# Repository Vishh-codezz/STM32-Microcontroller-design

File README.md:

# STM32-Microcontroller-design
This project is about the STM32 microcontroller board design.

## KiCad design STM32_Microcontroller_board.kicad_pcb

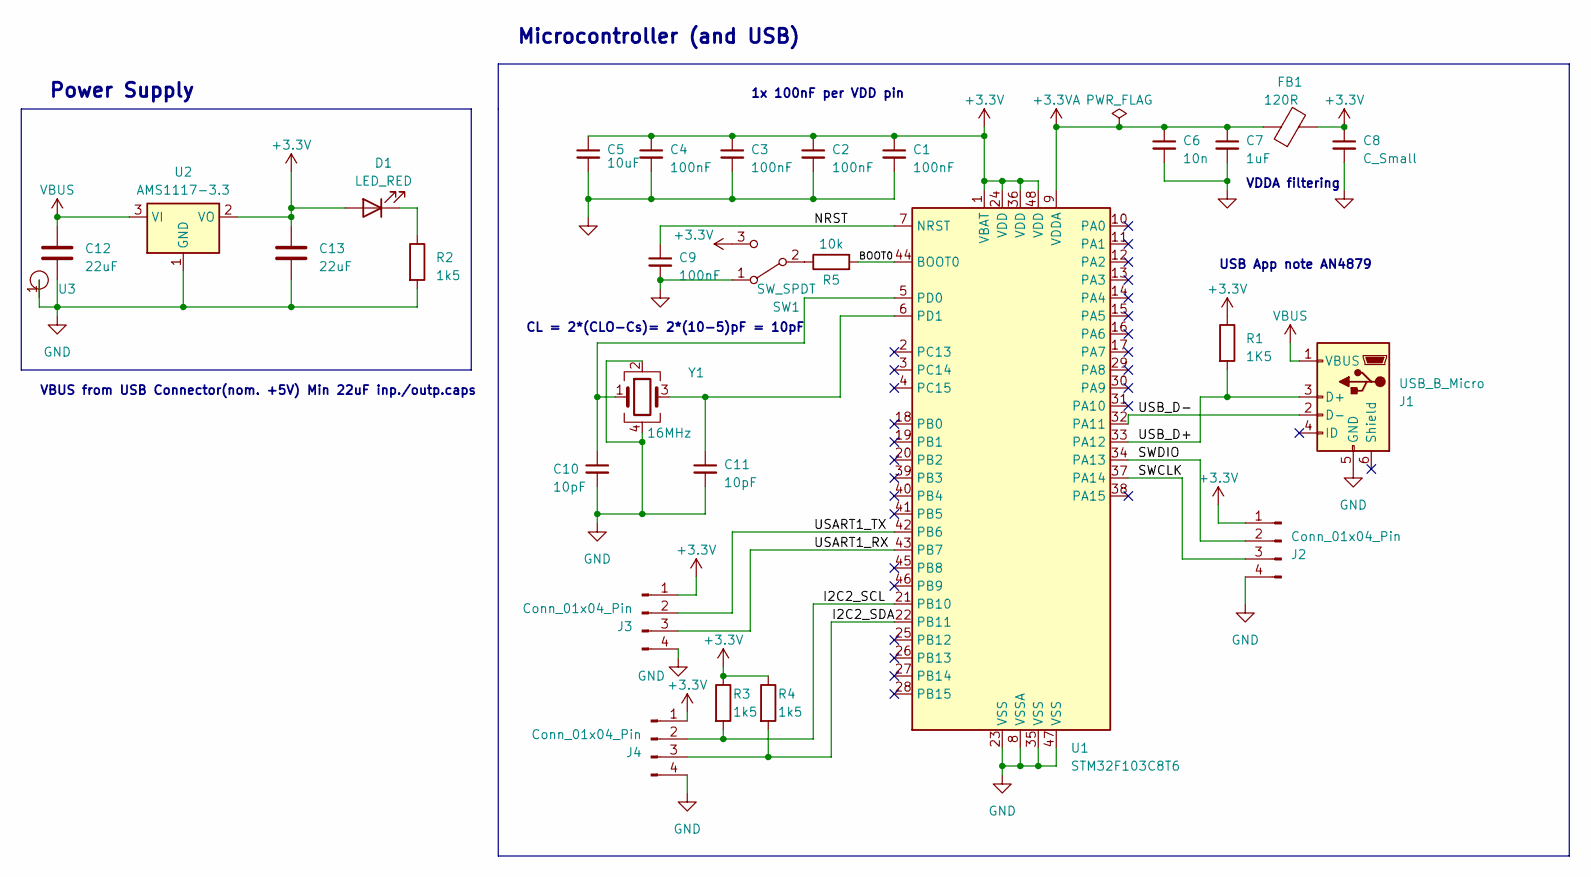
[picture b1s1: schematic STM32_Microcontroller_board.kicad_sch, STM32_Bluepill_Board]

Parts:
C1, C2, C3, C4, C9: 100nF; C_0402_1005Metric
C5: 10uF; C_0603_1608Metric
C6: 10n; C_0402_1005Metric
C7: 1uF; C_0402_1005Metric
C8: C_Small; C_0402_1005Metric
C10, C11: 10pF; C_0402_1005Metric
C12, C13: 22uF; C_0805_2012Metric
D1: LED_RED; LED_0603_1608Metric
FB1: 120R; L_0603_1608Metric
J1: USB_B_Micro; USB_Micro-B_Wuerth_629105150521
J2, J3, J4: Conn_01x04_Pin; PinHeader_1x04_P2.54mm_Vertical
R1: 1K5; R_0402_1005Metric
R2, R3, R4: 1k5; R_0402_1005Metric
R5: 10k; R_0402_1005Metric
SW1: SW_SPDT; SW_SPDT_PCM12
U1: STM32F103C8T6; LQFP-48_7x7mm_P0.5mm
U2: AMS1117-3.3; SOT-223-3_TabPin2
U3: Soldernail
Y1: 16MHz; Crystal_SMD_3225-4Pin_3.2x2.5mm

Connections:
+3.3V: C1.1, C2.1, C3.1, C4.1, C5.1, C8.1, C13.1, D1.2 (A), FB1.2, J2.1, J3.1, J4.1, R1.1, R3.1, R4.1, SW1.3 (C), U1.1 (VBAT), U1.24 (VDD), U1.36 (VDD), U1.48 (VDD), U2.2 (VO)
+3.3VA: C6.1, C7.1, FB1.1, U1.9 (VDDA)
/BOOT0: R5.2, U1.44 (BOOT0)
/I2C2_SCL: J4.2, R3.2, U1.21 (PB10)
/I2C2_SDA: J4.3, R4.2, U1.22 (PB11)
/NRST: C9.1, U1.7 (NRST)
/SWCLK: J2.3, U1.37 (PA14)
/SWDIO: J2.2, U1.34 (PA13)
/USART1_RX: J3.3, U1.43 (PB7)
/USART1_TX: J3.2, U1.42 (PB6)
/USB_D+: J1.3 (D+), R1.2, U1.33 (PA12)
/USB_D-: J1.2 (D-), U1.32 (PA11)
GND: C1.2, C2.2, C3.2, C4.2, C5.2, C6.2, C7.2, C8.2, C9.2, C10.2, C11.2, C12.2, C13.2, J1.5 (GND), J2.4, J3.4, J4.4, R2.2, SW1.1 (A), U1.8 (VSSA), U1.23 (VSS), U1.35 (VSS), U1.47 (VSS), U2.1 (GND), U3.1, Y1.2, Y1.4
unnamed: D1.1 (K), R2.1
unnamed: R5.1, SW1.2 (B)
unnamed: C10.1, U1.5 (PD0), Y1.1
unnamed: C11.1, U1.6 (PD1), Y1.3
VBUS: C12.1, J1.1 (VBUS), U2.3 (VI)

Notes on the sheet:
USB App note AN4879
Microcontroller (and USB)
VDDA filtering
CL = 2*(CLO-Cs)= 2*(10-5)pF = 10pF
VBUS from USB Connector(nom. +5V) Min 22uF inp./outp.caps
Power Supply
1x 100nF per VDD pin

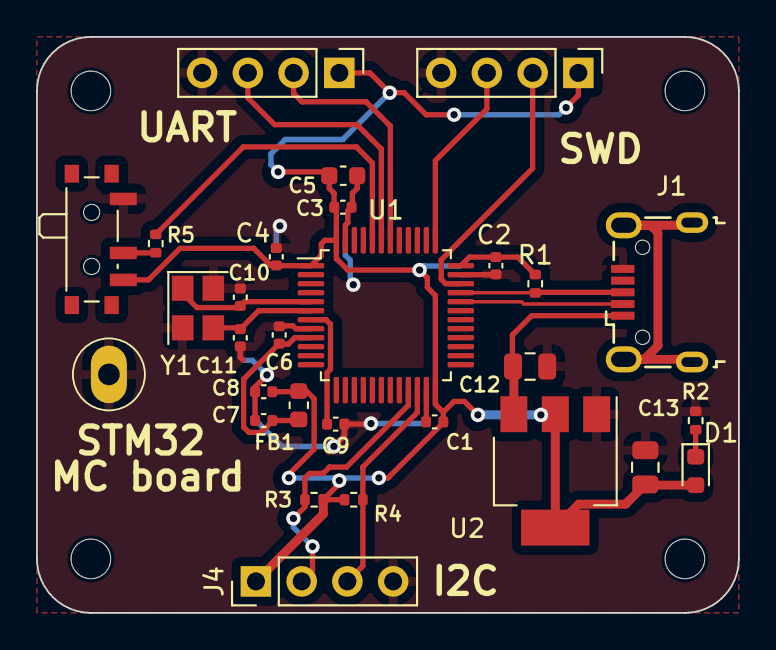
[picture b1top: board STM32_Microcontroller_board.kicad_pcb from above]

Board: 2 copper layers, 39.0 x 32.0 mm, 29 parts (0 on the bottom side), 18 nets.
